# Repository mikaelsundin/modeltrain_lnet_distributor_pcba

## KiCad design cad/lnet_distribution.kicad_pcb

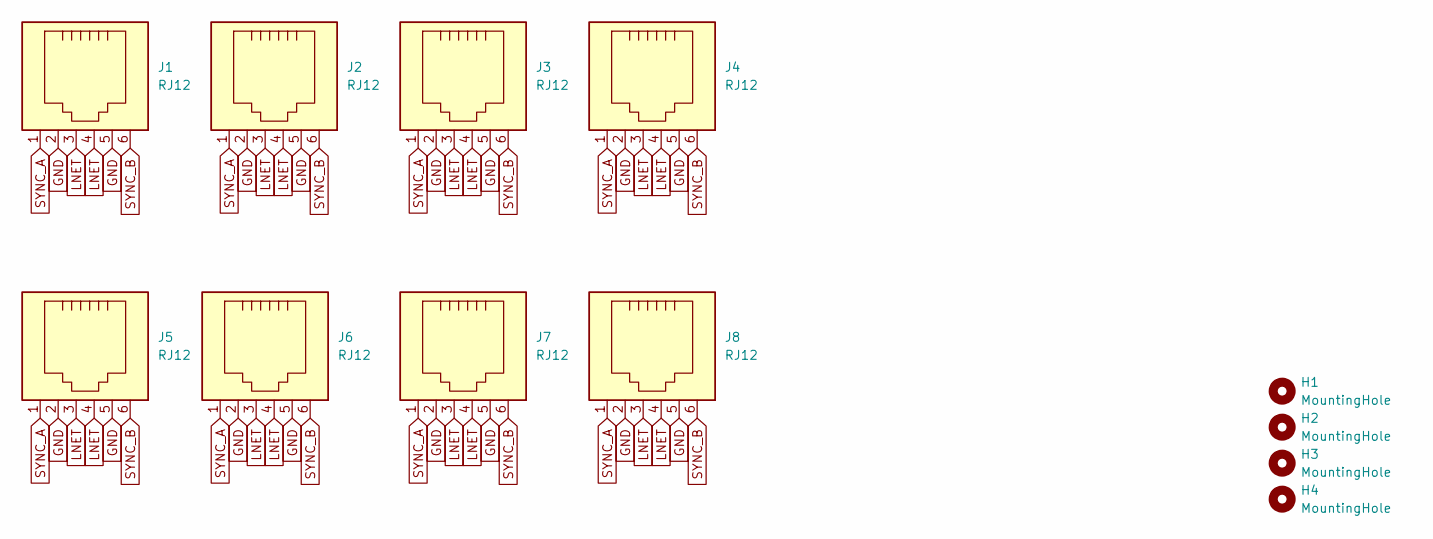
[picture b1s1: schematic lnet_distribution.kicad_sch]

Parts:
H1, H2, H3, H4: MountingHole; MountingHole_3.2mm_M3
J1, J2, J3, J4, J5, J6, J7, J8: RJ12

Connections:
GND: J1.2, J1.5, J2.2, J2.5, J3.2, J3.5, J4.2, J4.5, J5.2, J5.5, J6.2, J6.5, J7.2, J7.5, J8.2, J8.5
LNET: J1.3, J1.4, J2.3, J2.4, J3.3, J3.4, J4.3, J4.4, J5.3, J5.4, J6.3, J6.4, J7.3, J7.4, J8.3, J8.4
SYNC_A: J1.1, J2.1, J3.1, J4.1, J5.1, J6.1, J7.1, J8.1
SYNC_B: J1.6, J2.6, J3.6, J4.6, J5.6, J6.6, J7.6, J8.6

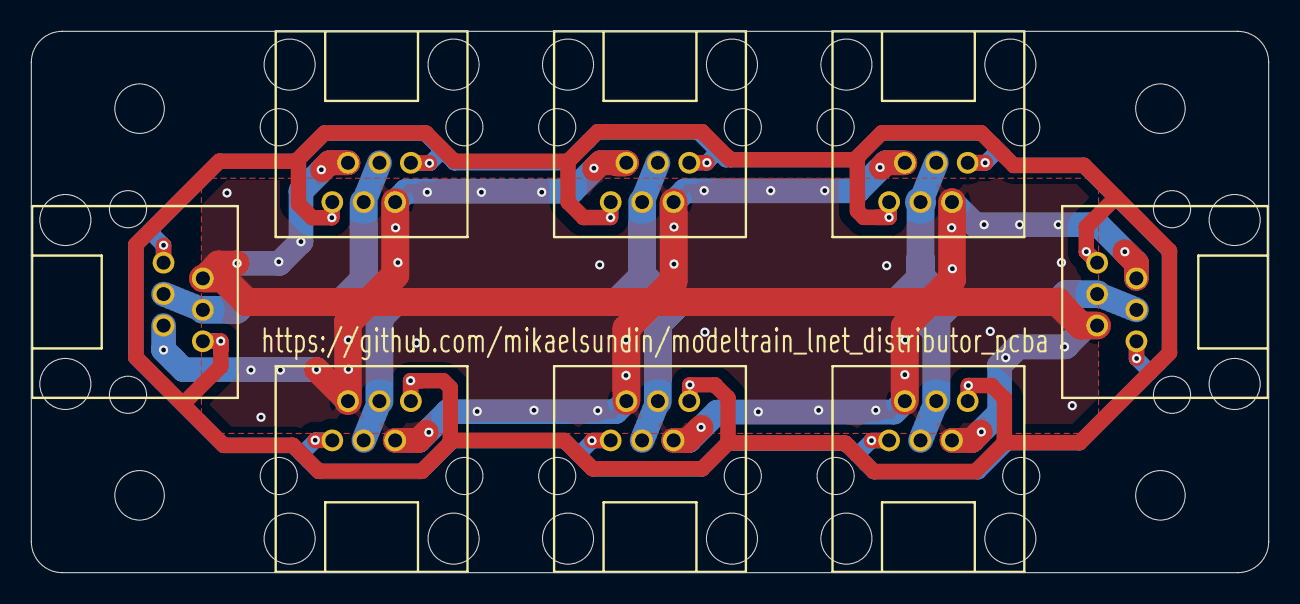
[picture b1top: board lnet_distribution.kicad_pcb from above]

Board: 2 copper layers, 80.0 x 35.0 mm, 12 parts (0 on the bottom side), 4 nets.

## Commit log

2026-05-16 LNET Distribution box cadded.
